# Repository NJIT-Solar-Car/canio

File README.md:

# CAN IO Board Development

# The CAN I/O driver board will allow the Central Control Unit to switch on and off various electronics over the vehicle’s CAN bus.

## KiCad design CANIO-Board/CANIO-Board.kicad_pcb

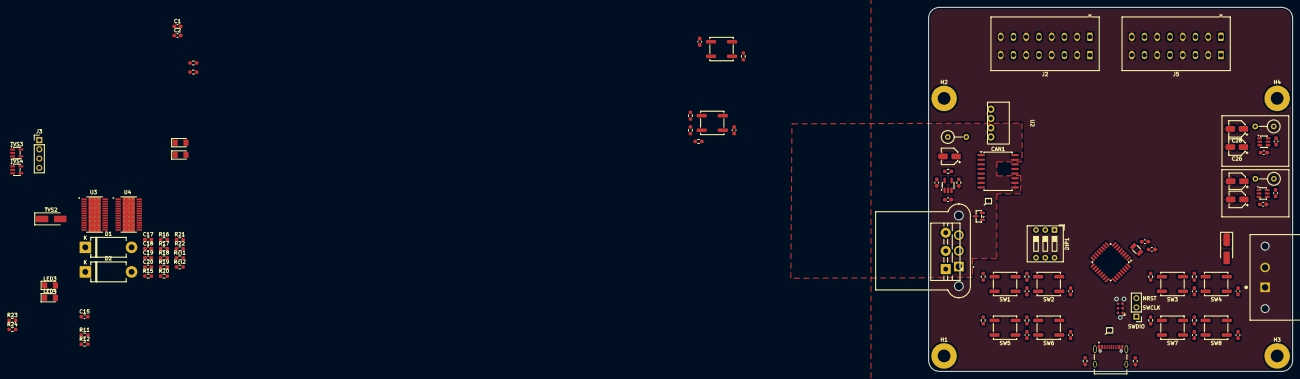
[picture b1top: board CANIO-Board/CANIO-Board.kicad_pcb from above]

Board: 4 copper layers, 100.0 x 100.0 mm, 111 parts (0 on the bottom side), 86 nets, no tracks yet.

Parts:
BUCK1: AP63203WU; TSOT-23-6
BUCK2: AP63205WU; TSOT-23-6
C1, C14, C16, C17, C19, C21, C22: 10u; C_0603_1608Metric_Pad1.08x0.95mm_HandSolder
C2, C18, C20, C23, C24: 100n; C_0603_1608Metric_Pad1.08x0.95mm_HandSolder
C3, C4: 22n; C_0603_1608Metric_Pad1.08x0.95mm_HandSolder
C5, C6, C7, C8, C9, C10, C11, C12, C29, C30: 1u; C_0603_1608Metric_Pad1.08x0.95mm_HandSolder
C13: 4.7u; CP_Elec_4x4.5
C15: 10n; C_0603_1608Metric_Pad1.08x0.95mm_HandSolder
C25, C26, C27, C28: 22u; CP_Elec_4x4.5
CAN1: ISO1042; SOIC-16W_7.5x10.3mm_P1.27mm
D1, D2: D; D_DO-201AD_P12.70mm_Horizontal
D3: D_TVS; D_SMA_Handsoldering
DIP1: SW_DIP_x03; SW_DIP_SPSTx03_Slide_9.78x9.8mm_W7.62mm_P2.54mm
DT1: Conn_01x03; TE_DTF13-3P
FILTER1, FILTER2: ECMF02-2AMX6; ECMF02-2AMX6_QFN-6L
H1, H2, H3, H4: MountingHole; MountingHole_3.5mm_Pad
J1: DT13-2P; TE_DTF13-2P
J2, J5: WAGO 2601; TerminalBlock_WAGO_2601-1108_1x08_P3.50mm_Horizontal
J3: Conn_01x04; PinHeader_1x04_P2.54mm_Vertical
J4: Conn_01x03; PinHeader_1x03_P2.54mm_Vertical
J7: Conn_01x03; TerminalBlock_MaiXu_MX126-5.0-03P_1x03_P5.00mm
L1: 47u; L_Axial_L7.0mm_D3.3mm_P5.08mm_Vertical_Fastron_MICC
L2, L3: 4.7u; L_Axial_L7.0mm_D3.3mm_P5.08mm_Vertical_Fastron_MICC
LDO1: SPX5205-ADJ; SOT-23-5_HandSoldering
LED1, LED2, LED3, LED4: LED_Small; LED_1206_3216Metric_Pad1.42x1.75mm_HandSolder
R1, R2, R23, R24: 1k; R_0603_1608Metric_Pad0.98x0.95mm_HandSolder
R3, R4, R5, R6, R7, R8, R9, R10, R11, R12, R14, R25, R26, R27, R28: 10k; R_0603_1608Metric_Pad0.98x0.95mm_HandSolder
R13: 17k; R_0603_1608Metric_Pad0.98x0.95mm_HandSolder
R15, R16, R17, R18, R19, R20, R21, R22: 4k7; R_0603_1608Metric_Pad0.98x0.95mm_HandSolder
R29, R30: 5.1k; R_0603_1608Metric_Pad0.98x0.95mm_HandSolder
Rcl1, Rcl2: 800; R_0603_1608Metric_Pad0.98x0.95mm_HandSolder
SW1, SW2, SW3, SW4, SW5, SW6, SW7, SW8, SW9, SW10: SW_Push; SW_Push_1P1T_NO_CK_KSC7xxJ
TC1: TC2030; Tag-Connect_TC2030-IDC-NL_2x03_P1.27mm_Vertical
TVS1: D_TVS_Dual_AAC; SOT-23
TVS2: D_TVS; D_SMA_Handsoldering
TVS3, TVS4: ESDS314DBVR; SOT-23-5
U1: STM32G0B1KETxN; LQFP-32_7x7mm_P0.8mm
U2: NME1; NME1S
U3, U4: TPS4H160AQPWPRQ1; IC_TPS4H160AQPWPRQ1
U5: SHOUHAN_TYPE-C_16PIN_2MD__073_
Y1: Crystal; Crystal_SMD_3215-2Pin_3.2x1.5mm

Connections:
3v3: BUCK1.1 (FB), C1.1, C2.1, C5.1, C6.1, C7.1, C8.1, C9.1, C10.1, C11.1, C12.1, C25.1, C27.1, CAN1.1 (VDD1), DIP1.4, DIP1.5, DIP1.6, L2.2, R23.1, SW1.2, SW2.2, SW3.2, SW4.2, SW5.2, SW6.2, SW7.2, SW8.2, TC1.1, U1.4 (VDD), U1.20 (VDD)
5v0: BUCK2.1 (FB), C26.1, C28.1, C29.1, L3.2, R24.1, SW9.2, U2.2 (Vin+)
12v: BUCK1.2 (EN), BUCK1.3 (IN), BUCK2.2 (EN), BUCK2.3 (IN), C21.1, C22.1, D1.2 (A), D2.2 (A), D3.2 (A2), J1.1, TVS2.1 (A1)
/CAN/CAN1_RX: CAN1.5 (RXD), U1.15 (PB0)
/CAN/CAN1_TX: CAN1.3 (TXD), U1.16 (PB1)
/CAN/CANH_+: DT1.1, FILTER1.1 (DP_C), J7.1, TVS1.2 (A2)
/CAN/CANL_-: DT1.2, FILTER1.2 (DN_C), J7.2, TVS1.1 (A1)
/CAN/FILTERED_CAN+: CAN1.13 (CANH), FILTER1.6 (DP_IC), R11.1
/CAN/FILTERED_CAN-: CAN1.12 (CANL), FILTER1.5 (DN_IC), R12.2
/Connectors/CAN_ADDR0: DIP1.3, U1.18 (PA8)
/Connectors/CAN_ADDR1: DIP1.2, U1.19 (PA9/UCPD1_DBCC1)
/Connectors/CAN_ADDR2: DIP1.1, U1.21 (PA10/UCPD1_DBCC2)
/Connectors/FAULT: R2.1, U1.14 (PA7)
/Connectors/GPIO0: J3.1, TVS3.1 (IN1), U1.26 (PD0)
/Connectors/GPIO1: J3.2, TVS3.3 (IN2), U1.27 (PD1)
/Connectors/GPIO2: J3.3, TVS3.4 (IN3), U1.28 (PD2)
/Connectors/GPIO3: J3.4, TVS3.5 (IN4), U1.17 (PB15)
/Connectors/HEARTBEAT: R1.1, U1.13 (PA6)
/Connectors/HighDrive1: J2.1, U3.27 (OUT1), U3.28 (OUT1)
/Connectors/HighDrive2: J2.3, U3.25 (OUT2), U3.26 (OUT2)
/Connectors/HighDrive3: J2.5, U3.17 (OUT3), U3.18 (OUT3)
/Connectors/HighDrive4: J2.7, U3.15 (OUT4), U3.16 (OUT4)
/Connectors/HighDrive5: J5.1, U4.27 (OUT1), U4.28 (OUT1)
/Connectors/HighDrive6: J5.3, U4.25 (OUT2), U4.26 (OUT2)
/Connectors/HighDrive7: J5.5, U4.17 (OUT3), U4.18 (OUT3)
/Connectors/HighDrive8: J5.7, U4.15 (OUT4), U4.16 (OUT4)
/Connectors/NRST: C30.1, J4.3, R28.1, TC1.6, TVS4.3 (IN2), U1.6 (PF2)
/Connectors/SWCLK: J4.2, TC1.4, TVS4.4 (IN3), U1.25 (PA14)
/Connectors/SWDIO: J4.1, TC1.2, TVS4.5 (IN4), U1.24 (PA13)
/Connectors/USBD+: FILTER2.2 (DN_C), U5.A6 (D+), U5.B6 (D+)
/Connectors/USBD-: FILTER2.1 (DP_C), U5.A7 (D-), U5.B7 (D-)
/Connectors/USB_DM-: FILTER2.6 (DP_IC), U1.22 (PA9/PA11)
/Connectors/USB_DP+: FILTER2.5 (DN_IC), U1.23 (PA10/PA12)
/Connectors/WKUP: C29.2, R25.1, R26.1, U1.7 (PA0)
/Load_Driver/HighChan1: C5.2, R3.1, R15.2, U1.29 (PD3)
/Load_Driver/HighChan2: C6.2, R4.1, R16.2, U1.30 (PB6)
/Load_Driver/HighChan3: C7.2, R5.1, R17.2, U1.31 (PB7)
/Load_Driver/HighChan4: C8.2, R6.1, R18.2, U1.32 (PB8)
/Load_Driver/HighChan5: C9.2, R7.1, U1.1 (PB9), U3.9 (ST3_FAULT_N)
/Load_Driver/HighChan6: C10.2, R8.1, R19.2, U1.8 (PA1)
/Load_Driver/HighChan7: C11.2, R9.1, R20.2, U1.9 (PA2)
/Load_Driver/HighChan8: C12.2, R10.1, R21.2, U1.10 (PA3)
/Load_Driver/HighChan9: R22.2, U1.11 (PA4)
/Load_Driver/HighChan10: U1.12 (PA5), U4.9 (ST3_FAULT_N)
/STM32G0B1/OSC32_IN: C3.1, U1.2 (PC14), Y1.1
/STM32G0B1/OSC32_OUT: C4.1, U1.3 (PC15), Y1.2
CANGND: C13.2, C14.2, C15.2, C16.2, CAN1.9 (GND2), CAN1.10 (GND2), CAN1.15 (GND2), FILTER1.3 (GND), FILTER1.4 (GND), LDO1.2 (GND), R14.2, TVS1.3 (common), U2.3 (Vout-)
CANVDD: C16.1, CAN1.11 (VDD2), CAN1.16 (VDD2), LDO1.5 (VOUT), R13.1
GND: BUCK1.4 (GND), BUCK2.4 (GND), C1.2, C2.2, C3.2, C4.2, C17.2, C18.2, C19.2, C20.2, C21.2, C22.2, C25.2, C26.2, C27.2, C28.2, C30.2, CAN1.2 (GND1), CAN1.8 (GND1), D3.1 (A1), DT1.3, FILTER2.3 (GND), FILTER2.4 (GND), J1.2, J2.2, J2.4, J2.6, J2.8, J5.2, J5.4, J5.6, J5.8, J7.3, LED1.1 (K), LED2.1 (K), LED3.1 (K), LED4.1 (K), R27.2, R29.1, R30.1, Rcl1.2, Rcl2.2, SW10.1, TC1.3, TC1.5, TVS2.2 (A2), TVS3.2 (GND), TVS4.2 (GND), U1.5 (VSS), U2.1 (Vin-), U3.1 (GND), U3.12 (GND), U3.13 (THER), U3.29 (PAD), U4.1 (GND), U4.12 (GND), U4.13 (THER), U4.29 (PAD), U5.A1_B12 (GND), U5.B1_A12 (GND), U5.SH1 (SHIELD), U5.SH2 (SHIELD), U5.SH3 (SHIELD), U5.SH4 (SHIELD)
unnamed: BUCK1.6 (BST), C23.2
unnamed: BUCK1.5 (SW), C23.1, L2.1
unnamed: BUCK2.6 (BST), C24.2
unnamed: BUCK2.5 (SW), C24.1, L3.1
unnamed: C15.1, R11.2, R12.1
unnamed: C17.1, C18.1, D1.1 (K), U3.20 (VS), U3.21 (VS), U3.22 (VS), U3.23 (VS)
unnamed: C19.1, C20.1, D2.1 (K), U4.20 (VS), U4.21 (VS), U4.22 (VS), U4.23 (VS)
unnamed: C13.1, C14.1, L1.2, LDO1.1 (5V), LDO1.3 (EN)
unnamed: LDO1.4 (ADJ), R13.2, R14.1
unnamed: LED1.2 (A), R1.2
unnamed: LED2.2 (A), R2.2
unnamed: LED3.2 (A), R23.2
unnamed: LED4.2 (A), R24.2
unnamed: R3.2, SW1.1
unnamed: R4.2, SW2.1
unnamed: R5.2, SW3.1
unnamed: R6.2, SW4.1
unnamed: R7.2, SW5.1
unnamed: R8.2, SW6.1
unnamed: R9.2, SW7.1
unnamed: R10.2, SW8.1
unnamed: R25.2, SW9.1
unnamed: R26.2, R27.1
unnamed: R28.2, SW10.2
unnamed: L1.1, U2.4 (Vout+)
unnamed: Rcl1.1, U3.11 (CL)
unnamed: R15.1, U3.3 (IN1)
unnamed: R16.1, U3.4 (IN2)
unnamed: R17.1, U3.5 (IN3)
unnamed: R18.1, U3.6 (IN4)
unnamed: Rcl2.1, U4.11 (CL)
unnamed: R19.1, U4.3 (IN1)
unnamed: R20.1, U4.4 (IN2)
unnamed: R21.1, U4.5 (IN3)
unnamed: R22.1, U4.6 (IN4)
unnamed: R29.2, U5.A5 (CC1)
unnamed: R30.2, U5.B5 (CC2)

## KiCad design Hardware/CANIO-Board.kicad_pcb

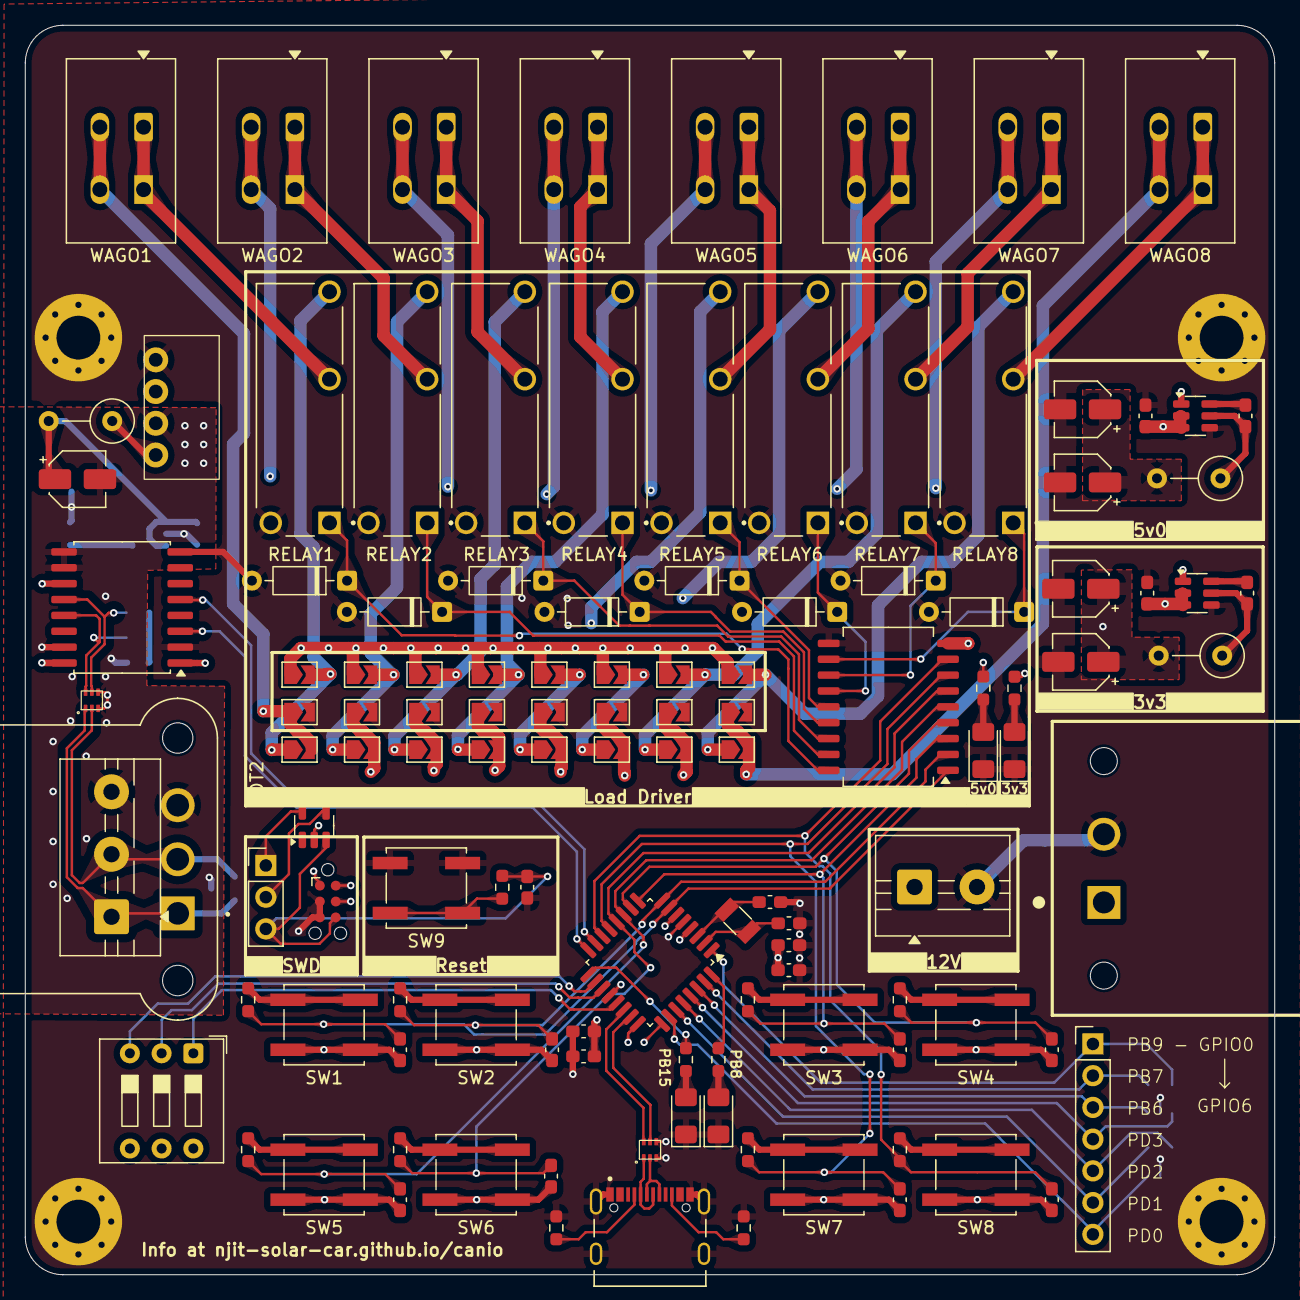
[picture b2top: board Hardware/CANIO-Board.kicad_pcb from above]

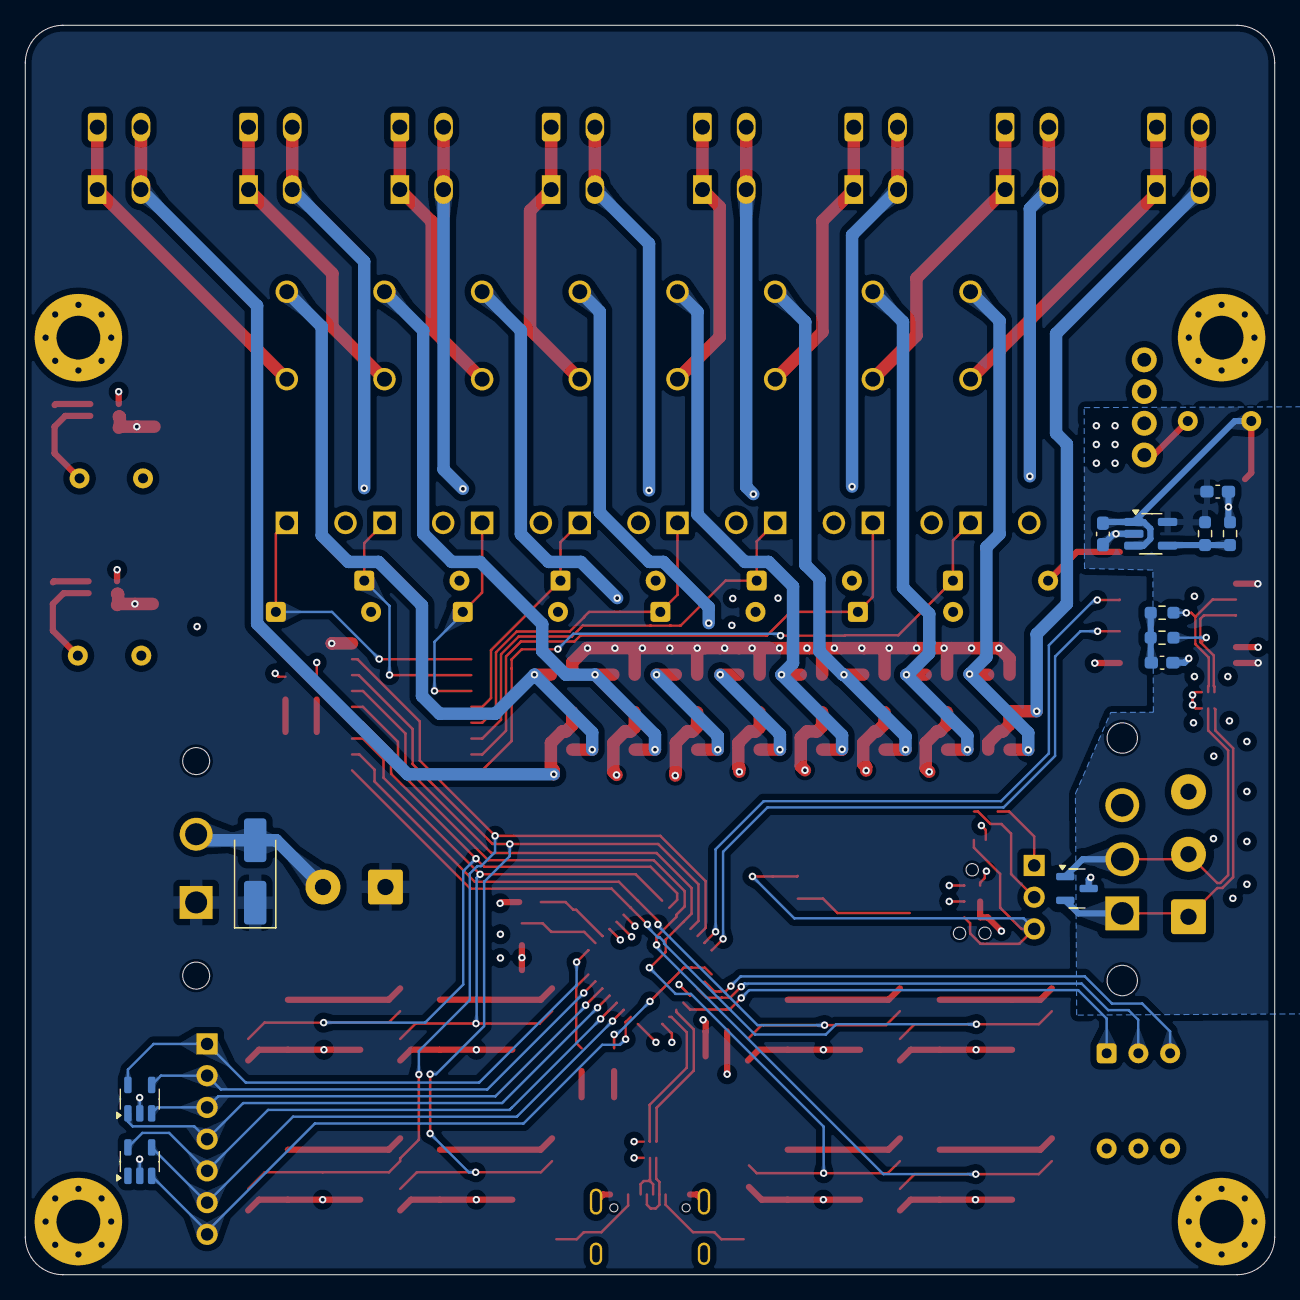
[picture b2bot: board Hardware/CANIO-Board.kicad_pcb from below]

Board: 4 copper layers, 100.0 x 100.0 mm, 138 parts (12 on the bottom side), 96 nets.

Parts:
BUCK1: AP63203QWU-7; TSOT-23-6
BUCK2: AP63205QWU-7; TSOT-23-6
C1, C2, C3, C4, C5, C6, C7, C8, C27: 1u; C_0603_1608Metric_Pad1.08x0.95mm_HandSolder
C9, C11, C18, C22, C23, C24: 10u; C_0603_1608Metric_Pad1.08x0.95mm_HandSolder
C10, C12, C15, C19: 100n; C_0603_1608Metric_Pad1.08x0.95mm_HandSolder
C13, C14: 22n; C_0603_1608Metric_Pad1.08x0.95mm_HandSolder
C16, C17, C20, C21: 22u; CP_Elec_4x4.5
C25: 4.7u; CP_Elec_4x4.5
C26: 10n; C_0603_1608Metric_Pad1.08x0.95mm_HandSolder
CAN1: ISO1042; SOIC-16W_7.5x10.3mm_P1.27mm
DCDC1: NME1; NME1S
DFB1, DFB2, DFB3, DFB4, DFB5, DFB6, DFB7, DFB8: D_Small; D_DO-35_SOD27_P7.62mm_Horizontal
DIP1: SW_DIP_x03; SW_DIP_SPSTx03_Slide_9.78x9.8mm_W7.62mm_P2.54mm
DT1: Conn_01x02; TE_DTF13-2P
DT2: Conn_01x03; TE_DTF13-3P
FILTER1, FILTER2: ECMF02-2AMX6; ECMF02-2AMX6_QFN-6L
H1, H2, H3, H4: GND; MountingHole_3.5mm_Pad_Via
J1: Conn_01x03; PinHeader_1x03_P2.54mm_Vertical
J2: Conn_01x07; PinHeader_1x07_P2.54mm_Vertical
L1, L2: 4.7u; L_Axial_L7.0mm_D3.3mm_P5.08mm_Vertical_Fastron_MICC
L3: 47u; L_Axial_L7.0mm_D3.3mm_P5.08mm_Vertical_Fastron_MICC
LDO1: SPX5205-ADJ; SOT-23-5_HandSoldering
LED1, LED2, LED3, LED4: LED_Small; LED_1206_3216Metric_Pad1.42x1.75mm_HandSolder
LOAD1: TBD62783AFWG; SOP-18_7x12.5mm_P1.27mm
MCU1: STM32G0B1KETxN; LQFP-32_7x7mm_P0.8mm
R1, R2, R3, R4, R5, R6, R7, R8, R14, R19: 10k; R_0603_1608Metric_Pad0.98x0.95mm_HandSolder
R9, R10, R11, R12: 1k; R_0603_1608Metric_Pad0.98x0.95mm_HandSolder
R13: 17k; R_0603_1608Metric_Pad0.98x0.95mm_HandSolder
R15, R16: 60; R_0603_1608Metric_Pad0.98x0.95mm_HandSolder
R17, R18: 5.1k; R_0603_1608Metric_Pad0.98x0.95mm_HandSolder
RELAY1, RELAY2, RELAY3, RELAY4, RELAY5, RELAY6, RELAY7, RELAY8: ALDP112W; RELAY_ALDP112W
SB1, SB2, SB3, SB4, SB5, SB6, SB7, SB8, SB9, SB10, SB11, SB12, SB13, SB14, SB15, SB16, SB17, SB18, SB19, SB20, SB21, SB22, SB23, SB24: SolderJumper_2_Open; SolderJumper-2_P1.3mm_Open_TrianglePad1.0x1.5mm
SCREW1: Conn_01x02; TerminalBlock_MaiXu_MX126-5.0-02P_1x02_P5.00mm
SCREW2: Conn_01x03; TerminalBlock_MaiXu_MX126-5.0-03P_1x03_P5.00mm
SW1, SW2, SW3, SW4, SW5, SW6, SW7, SW8, SW9: SW_Push; SW_Push_1P1T_NO_CK_KSC7xxJ
TC1: TC2030; Tag-Connect_TC2030-IDC-NL_2x03_P1.27mm_Vertical
TVS1: D_TVS; D_SMA_Handsoldering
TVS2: D_TVS_Dual_AAC; SOT-23
TVS3, TVS4, TVS5: ESDS314DBVR; SOT-23-5
USB1: USB_C_Receptacle_USB2.0_16P; SHOUHAN_TYPE-C_16PIN_2MD__073_
WAGO1, WAGO2, WAGO3, WAGO4, WAGO5, WAGO6, WAGO7, WAGO8: 2601; TerminalBlock_WAGO_2601-1102_1x02_P3.50mm_Horizontal
Y1: Crystal; Crystal_SMD_3215-2Pin_3.2x1.5mm

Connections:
3v3: BUCK1.1 (FB), C1.1, C2.1, C3.1, C4.1, C5.1, C6.1, C7.1, C8.1, C9.1, C10.1, C11.1, C12.1, C16.1, C17.1, CAN1.1 (VDD1), DIP1.4, DIP1.5, DIP1.6, L1.2, MCU1.4 (VDD), MCU1.20 (VDD), R11.1, SW1.2, SW2.2, SW3.2, SW4.2, SW5.2, SW6.2, SW7.2, SW8.2, TC1.1
5v0: BUCK2.1 (FB), C20.1, C21.1, DCDC1.2 (Vin+), L2.2, R12.1
+12V: BUCK1.2 (EN), BUCK1.3 (IN), BUCK2.2 (EN), BUCK2.3 (IN), C18.1, C22.1, DT1.1, LOAD1.9 (VCC), SB1.1 (A), SB2.1 (A), SB3.1 (A), SB4.1 (A), SB13.1 (A), SB14.1 (A), SB15.1 (A), SB16.1 (A), SCREW1.1, TVS1.1 (A1)
/CAN/CAN1_RX: CAN1.5 (RXD), MCU1.15 (PB0)
/CAN/CAN1_TX: CAN1.3 (TXD), MCU1.16 (PB1)
/CAN/CAN_+: DT2.1, FILTER1.1 (DP_C), SCREW2.1, TVS2.2 (A2)
/CAN/CAN_-: DT2.2, FILTER1.2 (DN_C), SCREW2.2, TVS2.1 (A1)
/CAN/FILTERED_CAN+: CAN1.13 (CANH), FILTER1.6 (DP_IC), R15.1
/CAN/FILTERED_CAN-: CAN1.12 (CANL), FILTER1.5 (DN_IC), R16.2
/Connectors/CAN_ADDR0: DIP1.3, MCU1.18 (PA8)
/Connectors/CAN_ADDR1: DIP1.2, MCU1.19 (PA9/UCPD1_DBCC1)
/Connectors/CAN_ADDR2: DIP1.1, MCU1.21 (PA10/UCPD1_DBCC2)
/Connectors/DriverOutN0: SB5.2 (B), SB9.1 (A), WAGO1.2
/Connectors/DriverOutN1: SB6.2 (B), SB10.1 (A), WAGO2.2
/Connectors/DriverOutN2: SB7.2 (B), SB11.1 (A), WAGO3.2
/Connectors/DriverOutN3: SB8.2 (B), SB12.1 (A), WAGO4.2
/Connectors/DriverOutN4: SB17.2 (B), SB21.1 (A), WAGO5.2
/Connectors/DriverOutN5: SB18.2 (B), SB22.1 (A), WAGO6.2
/Connectors/DriverOutN6: SB19.2 (B), SB23.1 (A), WAGO7.2
/Connectors/DriverOutN7: SB20.2 (B), SB24.1 (A), WAGO8.2
/Connectors/DriverOutP0: RELAY1.3, WAGO1.1
/Connectors/DriverOutP1: RELAY2.3, WAGO2.1
/Connectors/DriverOutP2: RELAY3.3, WAGO3.1
/Connectors/DriverOutP3: RELAY4.3, WAGO4.1
/Connectors/DriverOutP4: RELAY5.3, WAGO5.1
/Connectors/DriverOutP5: RELAY6.3, WAGO6.1
/Connectors/DriverOutP6: RELAY7.3, WAGO7.1
/Connectors/DriverOutP7: RELAY8.3, WAGO8.1
/Connectors/FAULT: MCU1.17 (PB15), R10.1
/Connectors/GPIO0: J2.1, MCU1.1 (PB9), TVS5.5 (IN4)
/Connectors/GPIO1: J2.2, MCU1.31 (PB7), TVS5.4 (IN3)
/Connectors/GPIO2: J2.3, MCU1.30 (PB6), TVS5.3 (IN2)
/Connectors/GPIO3: J2.4, MCU1.29 (PD3), TVS5.1 (IN1)
/Connectors/GPIO4: J2.5, MCU1.28 (PD2), TVS4.5 (IN4)
/Connectors/GPIO5: J2.6, MCU1.27 (PD1), TVS4.4 (IN3)
/Connectors/GPIO6: J2.7, MCU1.26 (PD0), TVS4.3 (IN2)
/Connectors/HEARTBEAT: MCU1.32 (PB8), R9.1
/Connectors/NRST: C27.1, J1.3, MCU1.6 (PF2), R19.1, TC1.6, TVS3.3 (IN2)
/Connectors/OSC32_IN: C13.1, MCU1.2 (PC14), Y1.1
/Connectors/OSC32_OUT: C14.1, MCU1.3 (PC15), Y1.2
/Connectors/SWCLK: J1.2, MCU1.25 (PA14), TC1.4, TVS3.4 (IN3)
/Connectors/SWDIO: J1.1, MCU1.24 (PA13), TC1.2, TVS3.5 (IN4)
/Connectors/USBD+: FILTER2.2 (DN_C), USB1.A6 (D+), USB1.B6 (D+)
/Connectors/USBD-: FILTER2.1 (DP_C), USB1.A7 (D-), USB1.B7 (D-)
/Connectors/USB_DF+: FILTER2.5 (DN_IC), MCU1.23 (PA10/PA12)
/Connectors/USB_DF-: FILTER2.6 (DP_IC), MCU1.22 (PA9/PA11)
/Load_Driver/Chan0: C1.2, LOAD1.1 (IN1), MCU1.7 (PA0), R1.1
/Load_Driver/Chan1: C2.2, LOAD1.2 (IN2), MCU1.8 (PA1), R2.1
/Load_Driver/Chan2: C3.2, LOAD1.3 (IN3), MCU1.9 (PA2), R3.1
/Load_Driver/Chan3: C4.2, LOAD1.4 (IN4), MCU1.10 (PA3), R4.1
/Load_Driver/Chan4: C5.2, LOAD1.5 (IN5), MCU1.11 (PA4), R5.1
/Load_Driver/Chan5: C6.2, LOAD1.6 (IN6), MCU1.12 (PA5), R6.1
/Load_Driver/Chan6: C7.2, LOAD1.7 (IN7), MCU1.13 (PA6), R7.1
/Load_Driver/Chan7: C8.2, LOAD1.8 (IN8), MCU1.14 (PA7), R8.1
/Load_Driver/Coil0: DFB1.1 (K), LOAD1.18 (OUT1), RELAY1.1
/Load_Driver/Coil1: DFB2.1 (K), LOAD1.17 (OUT2), RELAY2.1
/Load_Driver/Coil2: DFB3.1 (K), LOAD1.16 (OUT3), RELAY3.1
/Load_Driver/Coil3: DFB4.1 (K), LOAD1.15 (OUT4), RELAY4.1
/Load_Driver/Coil4: DFB5.1 (K), LOAD1.14 (OUT5), RELAY5.1
/Load_Driver/Coil5: DFB6.1 (K), LOAD1.13 (OUT6), RELAY6.1
/Load_Driver/Coil6: DFB7.1 (K), LOAD1.12 (OUT7), RELAY7.1
/Load_Driver/Coil7: DFB8.1 (K), LOAD1.11 (OUT8), RELAY8.1
CANGND: C23.2, C24.2, C25.2, C26.2, CAN1.9 (GND2), CAN1.10 (GND2), CAN1.15 (GND2), DCDC1.3 (Vout-), DT2.3, FILTER1.3 (GND), FILTER1.4 (GND), LDO1.2 (GND), R14.2, SCREW2.3, TVS2.3 (common)
CANVDD: C23.1, CAN1.11 (VDD2), CAN1.16 (VDD2), LDO1.5 (VOUT), R13.1
GND: BUCK1.4 (GND), BUCK2.4 (GND), C9.2, C10.2, C11.2, C12.2, C13.2, C14.2, C16.2, C17.2, C18.2, C20.2, C21.2, C22.2, C27.2, CAN1.2 (GND1), CAN1.8 (GND1), DCDC1.1 (Vin-), DFB1.2 (A), DFB2.2 (A), DFB3.2 (A), DFB4.2 (A), DFB5.2 (A), DFB6.2 (A), DFB7.2 (A), DFB8.2 (A), DT1.2, FILTER2.3 (GND), FILTER2.4 (GND), H1.1, H2.1, H3.1, H4.1, LED1.1 (K), LED2.1 (K), LED3.1 (K), LED4.1 (K), LOAD1.10 (GND), MCU1.5 (VSS), R17.1, R18.1, RELAY1.2, RELAY2.2, RELAY3.2, RELAY4.2, RELAY5.2, RELAY6.2, RELAY7.2, RELAY8.2, SB9.2 (B), SB10.2 (B), SB11.2 (B), SB12.2 (B), SB21.2 (B), SB22.2 (B), SB23.2 (B), SB24.2 (B), SCREW1.2, SW9.1, TC1.3, TC1.5, TVS1.2 (A2), TVS3.2 (GND), TVS4.2 (GND), TVS5.2 (GND), USB1.A1_B12 (GND), USB1.B1_A12 (GND), USB1.SH1 (SHIELD), USB1.SH2 (SHIELD), USB1.SH3 (SHIELD), USB1.SH4 (SHIELD)
unnamed: BUCK1.6 (BST), C15.2
unnamed: BUCK1.5 (SW), C15.1, L1.1
unnamed: BUCK2.6 (BST), C19.2
unnamed: BUCK2.5 (SW), C19.1, L2.1
unnamed: C26.1, R15.2, R16.1
unnamed: DCDC1.4 (Vout+), L3.1
unnamed: C24.1, C25.1, L3.2, LDO1.1 (5V), LDO1.3 (EN)
unnamed: LDO1.4 (ADJ), R13.2, R14.1
unnamed: LED1.2 (A), R9.2
unnamed: LED2.2 (A), R10.2
unnamed: LED3.2 (A), R11.2
unnamed: LED4.2 (A), R12.2
unnamed: R1.2, SW1.1
unnamed: R2.2, SW2.1
unnamed: R3.2, SW3.1
unnamed: R4.2, SW4.1
unnamed: R5.2, SW5.1
unnamed: R6.2, SW6.1
unnamed: R7.2, SW7.1
unnamed: R8.2, SW8.1
unnamed: R19.2, SW9.2
unnamed: RELAY1.4, SB1.2 (B), SB5.1 (A)
unnamed: RELAY2.4, SB2.2 (B), SB6.1 (A)
unnamed: RELAY3.4, SB3.2 (B), SB7.1 (A)
unnamed: RELAY4.4, SB4.2 (B), SB8.1 (A)
unnamed: RELAY5.4, SB13.2 (B), SB17.1 (A)
unnamed: RELAY6.4, SB14.2 (B), SB18.1 (A)
unnamed: RELAY7.4, SB15.2 (B), SB19.1 (A)
unnamed: RELAY8.4, SB16.2 (B), SB20.1 (A)
unnamed: R17.2, USB1.A5 (CC1)
unnamed: R18.2, USB1.B5 (CC2)

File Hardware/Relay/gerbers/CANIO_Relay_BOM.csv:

Qty,QtyWithExtra,Reference,Value,Manufacturer Name,Part Number,Description,Comment
1,1,BUCK1,AP63203QWU-7,Diodes Incorporated,AP63203QWU-7,"2A, 1.1MHz Buck DC/DC Converter, fixed 3.3V output voltage, TSOT-23-6",
1,1,BUCK2,AP63205QWU-7,Diodes Incorporated,AP63203QWU-7,"2A, 1.1MHz Buck DC/DC Converter, fixed 5.0V output voltage, TSOT-23-6",
9,15,"C1,C2,C3,C4,C5,C6,C7,C8,C27",1u,Samsung Electro-Mechanics,CL10B105KO8NNNC,"capacitor, small US symbol",
6,10,"C9,C11,C18,C22,C23,C24",10u,Samsung Electro-Mechanics,CL10X106MO8NRNC,"capacitor, small US symbol",
4,10,"C10,C12,C15,C19",100n,Samsung Electro-Mechanics,CL10B104KB8NNNC,"capacitor, small US symbol",
2,10,"C13,C14",22n,Samsung Electro-Mechanics,CL10B223KB8WPNC,"capacitor, small US symbol",
4,10,"C16,C17,C20,C21",22u,Würth Elektronik,865080140001,"capacitor, small US symbol",
1,5,C25,4.7u,Würth Elektronik,865080640004,"capacitor, small US symbol",
1,10,C26,10n,Samsung Electro-Mechanics,CL10B103KB8NNNC,"capacitor, small US symbol",
1,1,CAN1,ISO1042,Texas Instruments,ISO1042BDWR,,
2,4,"L1,L2",4.7u,Bourns Inc.,RLB0914-4R7ML,"Inductor, small symbol",
1,1,D1,diode,MCC (Micro Commercial Components),SK1045-LTP,reverse polarity doide,
1,1,DCDC1,NME1,Murata Power Solutions Inc.,NME1S0505SC,,
1,2,DIP1,SW_DIP_x03,CTS Electrocomponents,208-3,"3x DIP Switch, Single Pole Single Throw (SPST) switch, small symbol",
1,1,DT1,Conn_01x02,,,"Generic connector, single row, 01x02, script generated (kicad-library-utils/schlib/autogen/connector/)",Not available on digikey
1,2,SCREW1,Screw Terminal 1x2,Same Sky,TB002-500-02BE,,
1,1,DT2,Conn_01x03,TE Connectivity Deutsch Connectors,DTF13-3P,"Generic connector, single row, 01x03, script generated (kicad-library-utils/schlib/autogen/connector/)",
1,2,SCREW2,Screw Terminal 1x3,Same Sky,TB002-500-03BE,,
2,10,"FILTER1,FILTER2",ECMF02-2AMX6,STMicroelectronics,ECMF02-2AMX6,,Suggesting to get 10 bcoz these things are small and easy to lose/inhale
1,2,L3,47u,TDK,B82422H1473K000,"Inductor, small symbol",
1,5,LDO1,SPX5205-ADJ,"MaxLinear, Inc.",SPX5205M5-L/TR,,"Same thing, very small easy to lose'"
4,10,"LED1,LED2,LED3,LED4",LED_Small,Lite-On Inc.,LTST-C150KGKT,"Light emitting diode, small symbol","Green LED for power indication, heartbeat, etc."
4,10,"LED1,LED2,LED3,LED4",LED_Small,Lite-On Inc.,LTST-C150KRKT,"Light emitting diode, small symbol",RED OPTIONAL!!! If we wanna use different color LED
4,10,"LED1,LED2,LED3,LED4",LED_Small,Lite-On Inc.,LTW-150TK,"Light emitting diode, small symbol",YELLOW OPTIONAL!!! If we wanna use different color LED
1,1,LOAD1,TBD62783AFWG,Toshiba Semiconductor and Storage,"TBD62783AFWG,EL",,
1,1,MCU1,STM32G0B1KETxN,STMicroelectronics,STM32G0B1KET6N,"STMicroelectronics Arm Cortex-M0+ MCU, 512KB flash, 144KB RAM, 64 MHz, 1.7-3.6V, 29 GPIO, LQFP32",
10,10,"R1,R2,R3,R4,R5,R6,R7,R8,R14,R19",10k,Panasonic Industry,ERA-3AEB103V,"Resistor, small US symbol",
4,10,"R9,R10,R11,R12",1k,Panasonic Industry,ERA-3AEB102V,"Resistor, small US symbol",
1,10,R13,17k,Stackpole Electronics,RMCF0402FT17K8,"Resistor, small US symbol",17.8k
2,10,"R17,R18",5.1k,Yageo,RT0603FRD075K1L,"Resistor, small US symbol",
2,10,"R15,R16",60,Panasonic Industry,ERJ-3EKF60R4V,"Resistor, small US symbol",
8,8,"RELAY1,RELAY2,RELAY3,RELAY4,RELAY5,RELAY6,RELAY7,RELAY8",ALDP112W,Panasonic Electric Works,ALDP112W,,
9,10,"SW1,SW2,SW3,SW4,SW5,SW6,SW7,SW8,SW9",SW_Push,E-Switch,TL3301AF160QG,"Push button switch, generic, two pins",
1,1,TC1,TC2030,Tag-Connect LLC,"TC2030-MCP-NL
",Tag-Connect’s 6-pins connector,NL (no leg) version
1,1,TVS1,D_TVS,Bourns Inc.,P4SMA15A,Bidirectional transient-voltage-suppression diode,"12.8V RWM, ~14V breakdown, 20A TVS diode. Kinda overkill current wise."
1,5,TVS2,D_TVS_Dual_AAC,Comchip Technology,CPDT-12V,"Bidirectional dual transient-voltage-suppression diode, center on pin 3",SOT-23-3. Easy to lose so get a ton
3,5,"TVS3,TVS4,TVS5",ESDS314DBVR,Texas Instruments,ESDS314DBVR,,
1,5,USB1,USB_C_Receptacle_USB2.0_16P,Same Sky,UJ20-C-H-G-SMT-1-P16-TR,USB 2.0-only 16P Type-C Receptacle connector,"Have had trouble soldering these in the past, get extra just in case."
8,10,"WAGO1,WAGO2,WAGO3,WAGO4,WAGO5,WAGO6,WAGO7,WAGO8",2601,WAGO Corporation,2601-1102,"Generic connector, single row, 01x02, script generated (kicad-library-utils/schlib/autogen/connector/)",Getting 10 (box) instead of 8 saves 2 bucks on digikey
1,5,Y1,Crystal,Abracon LLC,ABS07-32.768KHZ-T,Two pin crystal,"again, extra just in case"

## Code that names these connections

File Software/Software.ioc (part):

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Mcu.Name=STM32G0B1K(B-C-E)TxN
Mcu.Package=LQFP32
Mcu.UserName=STM32G0B1KETxN
PA0.GPIOParameters=GPIO_Label
PA0.GPIO_Label=HighChan0
PA0.Signal=GPIO_Output
PA1.GPIOParameters=GPIO_Label
PA1.GPIO_Label=HighChan1
PA1.Signal=GPIO_Output
PA10.GPIOParameters=GPIO_Label
PA10.GPIO_Label=CAN_ADDR2
PA10.Signal=GPIO_Input
PA11\ [PA9].Mode=Device
PA11\ [PA9].Signal=USB_DM
PA12\ [PA10].Mode=Device
PA12\ [PA10].Signal=USB_DP
PA13.Mode=Serial_Wire
PA13.Signal=SYS_SWDIO
PA14-BOOT0.Mode=Serial_Wire
PA14-BOOT0.Signal=SYS_SWCLK
PA2.GPIOParameters=GPIO_Label
PA2.GPIO_Label=HighChan2
PA2.Signal=GPIO_Output
PA3.GPIOParameters=GPIO_Label
PA3.GPIO_Label=HighChan3
PA3.Signal=GPIO_Output
PA4.GPIOParameters=GPIO_Label
PA4.GPIO_Label=HighChan4
PA4.Signal=GPIO_Output
PA5.GPIOParameters=GPIO_Label
PA5.GPIO_Label=HighChan5
PA5.Signal=GPIO_Output
PA6.GPIOParameters=GPIO_Label
PA6.GPIO_Label=HighChan6
PA6.Signal=GPIO_Output
PA7.GPIOParameters=GPIO_Label
PA7.GPIO_Label=HighChan7
PA7.Signal=GPIO_Output
PA8.GPIOParameters=GPIO_Label
PA8.GPIO_Label=CAN_ADDR0
PA8.Signal=GPIO_Input
PA9.GPIOParameters=GPIO_Label
PA9.GPIO_Label=CAN_ADDR1
PA9.Signal=GPIO_Input
PB0.Mode=FDCAN_Activate
PB0.Signal=FDCAN2_RX
PB1.Mode=FDCAN_Activate
PB1.Signal=FDCAN2_TX
PB15.GPIOParameters=GPIO_Label
PB15.GPIO_Label=FAULT
PB15.Signal=GPIO_Output
PB6.GPIOParameters=GPIO_Label
PB6.GPIO_Label=GPIO2
PB6.Signal=GPIO_Input
PB7.GPIOParameters=GPIO_Label
PB7.GPIO_Label=GPIO1
PB7.Signal=GPIO_Input
PB8.GPIOParameters=GPIO_Label
PB8.GPIO_Label=HEARTBEAT
PB8.Signal=GPIO_Output
PB9.GPIOParameters=GPIO_Label
PB9.GPIO_Label=GPIO0
PB9.Signal=GPIO_Input
PC14-OSC32_IN\ (PC14).Mode=LSE-External-Oscillator
PC14-OSC32_IN\ (PC14).Signal=RCC_OSC32_IN
PC15-OSC32_OUT\ (PC15).Mode=LSE-External-Oscillator
PC15-OSC32_OUT\ (PC15).Signal=RCC_OSC32_OUT
PD0.GPIOParameters=GPIO_Label
PD0.GPIO_Label=GPIO6
PD0.Signal=GPIO_Input
PD1.GPIOParameters=GPIO_Label
PD1.GPIO_Label=GPIO5
PD1.Signal=GPIO_Input
PD2.GPIOParameters=GPIO_Label
PD2.GPIO_Label=GPIO4
PD2.Signal=GPIO_Input
PD3.GPIOParameters=GPIO_Label
PD3.GPIO_Label=GPIO3
PD3.Signal=GPIO_Input
RCC.HSE_VALUE=8000000
RCC.SYSCLKFreq_VALUE=16000000
board=custom

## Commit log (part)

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2026-06-08 updated the changelog
2026-06-08 Added initial provided schematics
2026-06-08 added Logo and TPL7407 datasheet
2026-06-08 Restructured the schematic a little for modularity
    - Gave each sub-component its own hierarchical sheet
    - Placed the current schematic into a temporary sheet called 'old'.
    Gonna adapt everything and double check while doing so.
    - Will make one commit with adapted schematic.
2026-06-08 added some more datasheets and a button debouncing AN from TI
2026-06-09 Added Relay Driver schematics
    - added the ICs, relay sockets, etc
2026-06-09 sosbos/
2026-06-09 Finished the ISOW1044 Schematic
    - Ported over Kostadin's schematic
2026-06-09 Added more documentation datasheets
2026-06-09 Updated the IOC. Final IOC unless any schematic changes have to be made
2026-06-09 Finished final touches on schematic.
    - Schematic is complete (NOT yet checked by Yassa/Val)
    - ERC check is complete, understandable errors excused w/ comments
    - Final schematic formatting complete
2026-06-09 Added schematic pdf
2026-06-09 Updated IOC. didn't save cubemx before previous commit
2026-06-10 Added BOM v1. INCOMPLETE!!!
2026-06-10 Replaced the ISOW1044 CAN Transceiver with the ISO1042 + isolated DC-DC and LDO
2026-06-11 Updated the USB-C connector from 14 pin to 16 pin
2026-06-11 Updated CubeMX to G0B1KET6N
2026-06-11 Replaced G0B1KET6 with KET6N in schematic
    - Updated the schematic with new symbol and pinout.
    - Updated the rest of the schematic with all resulting changes
    - This includes the 8 output channels, 7 GPIOs, and slightly
    different WAGO connector configuration.
2026-06-11 Made the common mode choke footprint
2026-06-11 Replaced buck converters with drop in replacements
2026-06-11 Updated the gitignore (first commit software branch)
2026-06-11 Generated code from CubeMX
2026-06-15 Finished the board
    - Board layout and routing is finished. Need to fix ~30 ERC errors and
    add thorough notes throughout, but otherwise that's it.
    - Once ERC errors are resolved, will post BOM and Gerbers as a release.
2026-06-15 Fixed ERC errors
2026-06-15 Updated schematic and layout PDFs
2026-06-16 Cleaned up unused datasheets
2026-06-16 final changes on pcb
2026-06-16 added gerbers, drill files, and BOM
2026-06-16 Added the BOM
2026-06-16 added docs/index.html
2026-06-16 moved folders
2026-06-16 added doxygen group to main.c file
2026-06-16 added initial generated doxygen
2026-06-18 Update README with project details
    Added project details about the CAN I/O driver board functionality.
2026-06-18 Fix formatting in README.md
2026-06-18 Did some of the layout
2026-06-21 added labels to SWD header pins
2026-06-21 regenerated gerbers
